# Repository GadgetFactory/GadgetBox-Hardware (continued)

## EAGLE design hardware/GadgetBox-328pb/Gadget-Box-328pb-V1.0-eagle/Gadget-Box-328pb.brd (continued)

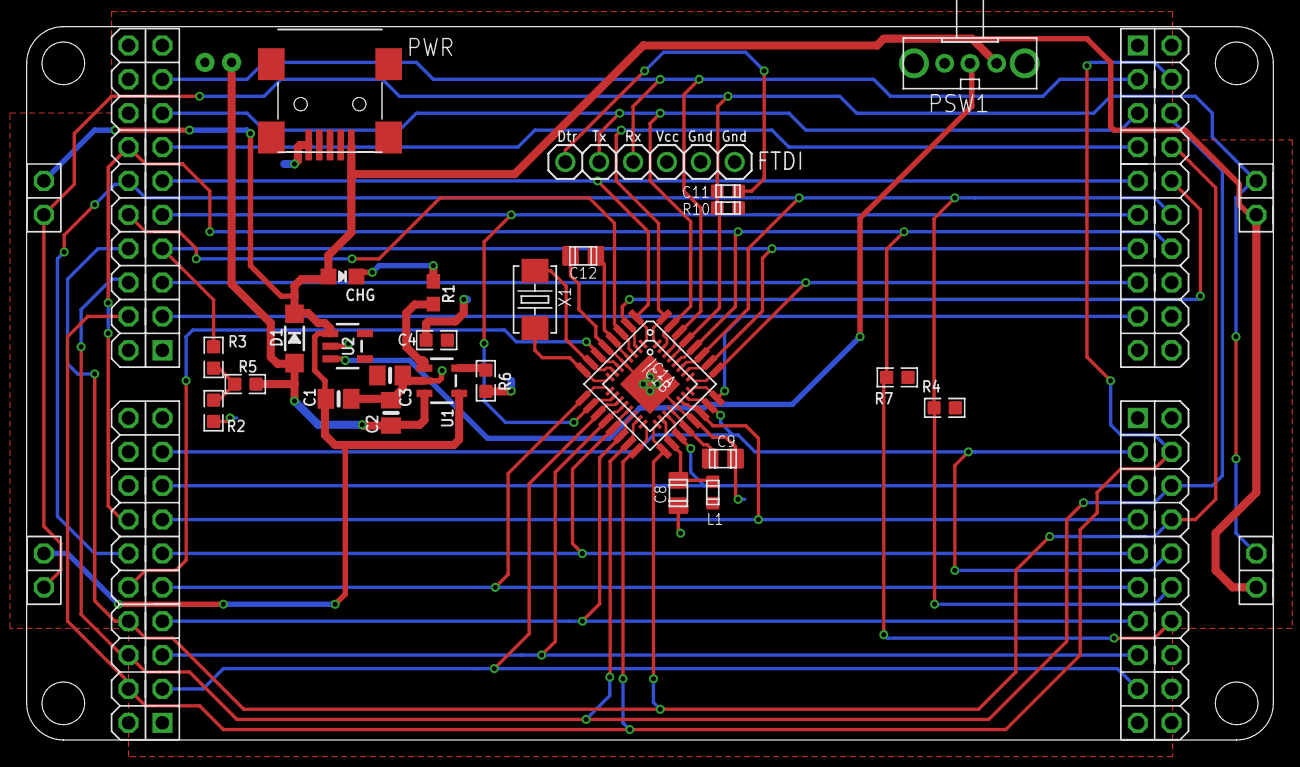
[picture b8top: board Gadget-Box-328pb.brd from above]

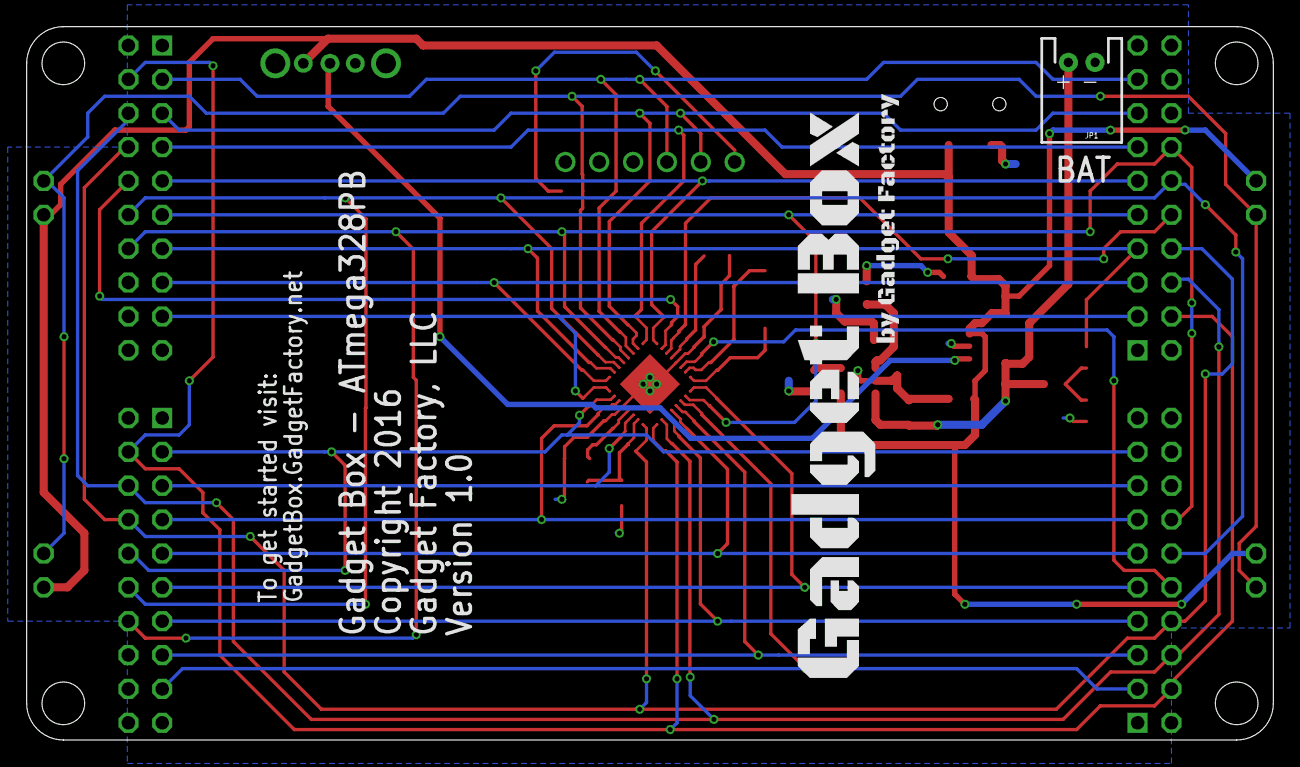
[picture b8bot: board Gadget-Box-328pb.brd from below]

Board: 2 copper layers, 93.5 x 53.5 mm, 34 parts (2 on the bottom side), 39 nets.

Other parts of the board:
$$U$1: ECOG93P53P5
U$100: GADGETBOX_TEXT

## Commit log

2016-10-28 :octocat: Added .gitattributes & .gitignore files
2016-10-28 Ignores
2016-10-28 Check in all hardware designs
2016-10-28 Changelog
2016-11-29 Connect VCC from USB connector to 5V0. Ooops!
2016-11-30 add eagle backup files to .gitignore
2016-11-30 minor typo in schematic note
2016-11-30 Added Proto_PTH v1
2016-12-01 silk adjustments
    moved bottom silk labels to edge
    replaced pin usage symols with sharpie area
2016-12-01 eCog002_Proto_SMD v1.0 added
2016-12-01 WIP Propeller
    still needs EEPROM, Crystal, Routing
2016-12-02 mostly done routing
    added EEPROM and most routing
2016-12-03 Propeller mostly done
    Need to validate FTDI connection and do eCog graphics
2016-12-04 WIP on 32u4
    flipping to standard layout
2016-12-04 more 32u4 progress
    50 airwires left
2016-12-05 traces done, beeds labels straightened
2016-12-05 cleaned up drc
2016-12-06 32u4 V1.8
    still needs top silk
2016-12-07 Added top silkscreen to layer 200.
2016-12-07 Papilio Flex for GadgetBox
2016-12-08 Battery Charging circuit added.
2016-12-08 updated eCog connectors to newer version footprint
    finor rerouting and other minor repair of an airwire
2016-12-08 updated eCog connectors to newer version footprint
    minor rerouting and other minor repair of an airwire
2016-12-08 Fully routed and passing drc
2016-12-08 Version 1.0 - Gadget Flex
2016-12-08 GadgetBox 328pb Version 1.3
2016-12-08 Removed Alt eCog headers and re-routed outside traces.
2016-12-08 Increased the size of the pads on the battery charge unit to allow surface mount soldering.
2016-12-09 Update eCogs to through hole
2016-12-09 Change to through hole and give bette descriptions.
2016-12-09 Put connector for both types of power schemes.
2016-12-09 Update board numbering.
2016-12-09 Added battery cutouts and re-routed everything.
2016-12-09 Name change
2016-12-09 Misc changes for manufacturing.
2016-12-12 Add Gitter badge
2016-12-13 Updated all of the templates numbering.
2016-12-13 Added eCogs for LogicStart Snap Pack for Papilio Flex
2016-12-13 Updated numbering scheme
2016-12-14 Better Readme
2017-01-13 Temp Sensor
